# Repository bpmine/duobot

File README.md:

# duobot

## Introduction

Ce projet est un n-ième clone du célèbre "self balancing robot" que l'on peut voir un peut partout sur Internet.

Voici un lien vers le projet original: https://electricdiylab.com/diy-self-balancing-robot/

Pour ce projet, nous conservons les fondamentaux de l'original (moteur, drivers, accéléromètre, ...).

Nous utiliserons les matériaux et les outils à notre à notre disposition. Les dimensions du robot seront également les nôtres.

Et la carte sera développée dans le but d'être utilisée pour d'autres applications similaires et pour permettre la mise au point d'autres projets à base de moteurs pas-à-pas.

## Construction du robot

## Conception de la carte

### Schéma

Presque un copier-coller du modèle d'origine.

Les différences principales sont les suivantes:
- Pull up sur le Enable plutôt que des pull-down sur le Step de chaque driver;
- Branchement des M0, M1 et M2 sur l'arduino (pour permettre le réglage de la résolution);
- Possibilité de brancher soit un drv4988 (comme l'original), soit un drv8825 (broche VDD ou Fault que l'on peut connecter grâce à des résistances 0 Ohms);
- Ajout de condensateurs de découplage (comme préconisé dans la datasheet des drivers);
- Sortie des broches non utilisées sur un connecteur d'extension.

### Routage du PCB

Complètement revu pour une carte moins dense (un peu plus grande) de 100mm x 70mm.
Les connecteurs seront des borniers plutôt que des JST comme sur le modèle. Ca permet un peu plus de souplesse lors des essais...

### Vue en 3D

## Mise en service

### Réglage du courant MAX

On tourne le potentiomètre des drivers jusqu'à obtenir 1V. Cela correspond à 250mA environ. Ce réglage sera à afiner en fonction des performances et de la limite admissible par le moteur...

### Programme de test de la carte

Le programme permet de tester la carte.

- Il affiche les valeurs lues sur l'accéléromètre
- il permet d'actionner les moteurs à l'aide des commandes.

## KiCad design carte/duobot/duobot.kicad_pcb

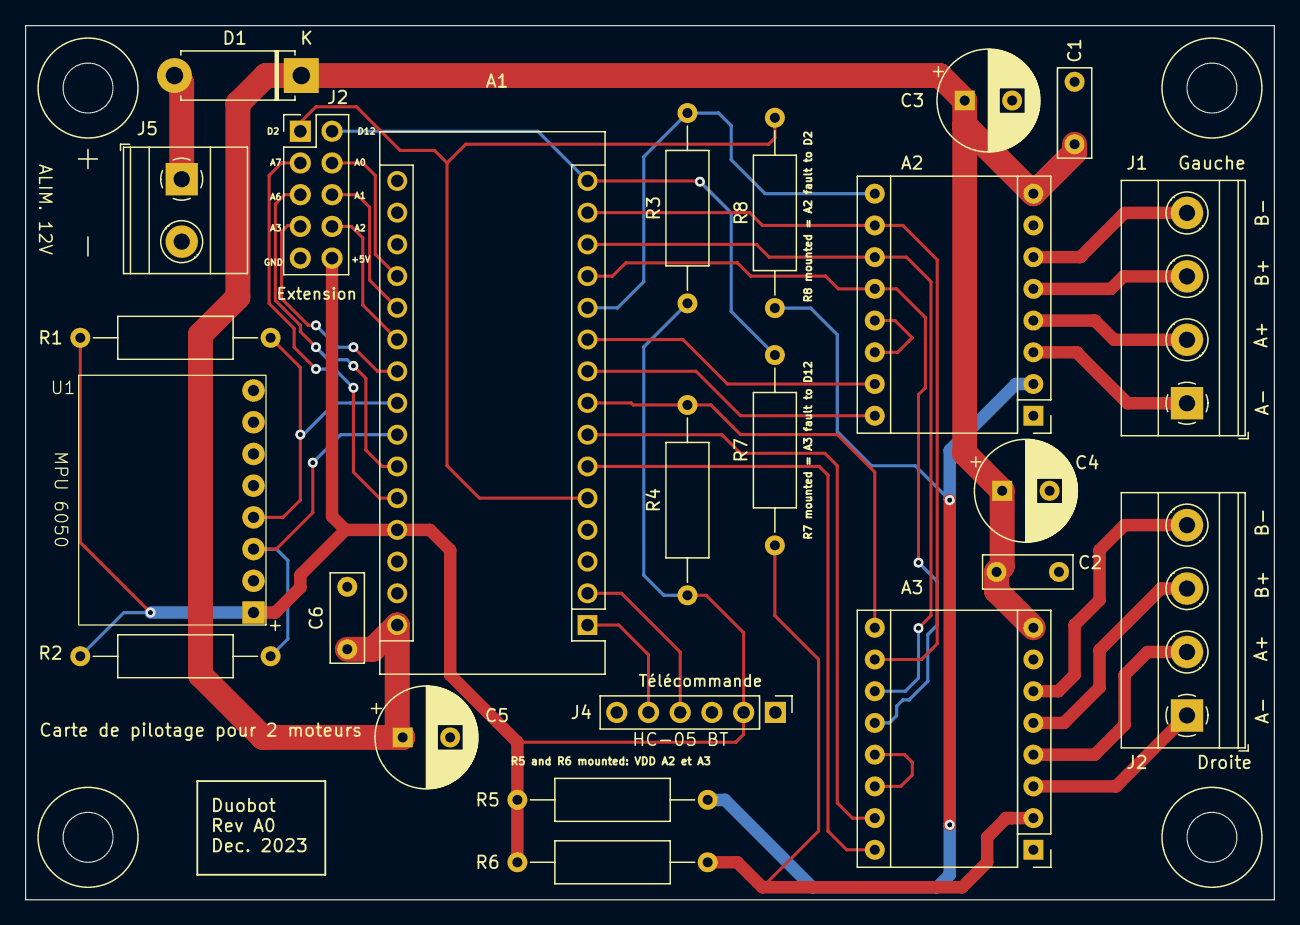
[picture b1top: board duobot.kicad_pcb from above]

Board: 2 copper layers, 100.0 x 70.0 mm, 28 parts (0 on the bottom side), 37 nets.

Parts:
A1: Arduino_Nano_v3.x; BPC_Arduino_Nano
A2, A3: BPC_Module-16_15.2x20.3mm
C1, C2: 100n; C_Disc_D7.0mm_W2.5mm_P5.00mm
C3, C4: 100uF; CP_Radial_D8.0mm_P3.80mm
C5: 20uF; CP_Radial_D8.0mm_P3.80mm
C6: 1n; C_Disc_D7.0mm_W2.5mm_P5.00mm
D1: D; D_5W_P10.16mm_Horizontal
J1: Moteur Gauche; TerminalBlock_Phoenix_MKDS-1,5-4-5.08_1x04_P5.08mm_Horizont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
J2: Moteur Droite; TerminalBlock_Phoenix_MKDS-1,5-4-5.08_1x04_P5.08mm_Horizont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
J2#2: Extension; PinHeader_2x05_P2.54mm_Vertical
J4: HC05 - BT; PinHeader_1x06_P2.54mm_Vertical
J5: Batterie; TerminalBlock_Phoenix_MKDS-1,5-2_1x02_P5.00mm_Horizontal
R1, R2: 10k; R_Axial_DIN0309_L9.0mm_D3.2mm_P15.24mm_Horizontal
R3, R4: 100k; R_Axial_DIN0309_L9.0mm_D3.2mm_P15.24mm_Horizontal
R5, R6, R7, R8: 0; R_Axial_DIN0309_L9.0mm_D3.2mm_P15.24mm_Horizontal
U1: BPC_MPU6050
X1, X2, X3, X4: Trou; BPC_Trou4mm_Fixation

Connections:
+5V: A1.27 (+5V), J2#2.10, J4.2, R1.1, R2.2, R3.1, R4.1, R5.2, R6.2, U1.1 (Vcc)
A0: A1.19 (A0), J2#2.4
A1: A1.20 (A1), J2#2.6
A2: A1.21 (A2), J2#2.8
A3: A1.22 (A3), J2#2.7
A6: A1.25 (A6), J2#2.5
A7: A1.26 (A7), J2#2.3
D2: A1.5 (D2), J2#2.1, R8.2
D12: A1.15 (D12), J2#2.2, R7.2
DIR_Droite: A1.6 (D3), A3.16 (DIR)
DIR_Gauche: A1.9 (D6), A2.16 (DIR)
EN_Droite: A1.8 (D5), A3.9 (~ENABLE), R4.2
EN_Gauche: A1.11 (D8), A2.9 (~ENABLE), R3.2
GND: A1.4 (GND), A1.29 (GND), A2.1 (GND), A2.7 (GND), A3.1 (GND), A3.7 (GND), C1.2, C2.2, C3.2, C4.2, C5.2, C6.2, J2#2.9, J4.3, J5.2, U1.2 (Gnd)
M0: A1.14 (D11), A2.10 (MS1), A3.10 (MS1)
M1: A1.13 (D10), A2.11 (MS2), A3.11 (MS2)
M2: A1.12 (D9), A2.12 (MS3), A3.12 (MS3)
unnamed: A1.2 (D0/RX), J4.4
unnamed: A1.1 (D1/TX), J4.5
unnamed: A1.30 (VIN), A2.8 (VMOT), A3.8 (VMOT), C1.1, C2.1, C3.1, C4.1, C5.1, C6.1, D1.1 (K)
unnamed: A2.4 (1A), J1.2
unnamed: A2.3 (1B), J1.1
unnamed: A2.5 (2A), J1.3
unnamed: A2.6 (2B), J1.4
unnamed: A2.2 (VDD), R5.1, R8.1
unnamed: A2.13 (~RESET), A2.14 (~SLEEP)
unnamed: A3.4 (1A), J2.2
unnamed: A3.3 (1B), J2.1
unnamed: A3.5 (2A), J2.3
unnamed: A3.6 (2B), J2.4
unnamed: A3.2 (VDD), R6.1, R7.1
unnamed: A3.13 (~RESET), A3.14 (~SLEEP)
unnamed: D1.2 (A), J5.1
SCL: A1.24 (A5), R2.1, U1.3 (SCL)
SDA: A1.23 (A4), R1.2, U1.4 (SDA)
STEP_Droite: A1.7 (D4), A3.15 (STEP)
STEP_Gauche: A1.10 (D7), A2.15 (STEP)

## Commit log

2023-12-16 Création pièce pour fixation roue
2023-12-17 Création de la carte de pilotage du robot
    Empreintes de l'accéléromètre et du module bluetooth à revoir avant envoi
2023-12-17 Finalisation routage et schéma
2023-12-17 Correction suite analyse des règles PCB
2023-12-26 Carte: Petite correction référence R5 et R8 sur le schéma Création du programme de test de la carte: OK
2023-12-29 first step to remove duplicate code
    not tested.
2023-12-29 Update duobot_test.ino
    rewriting
2023-12-29 Update duobot_test.ino
    remove repetitiion
2023-12-29 Update duobot_test.ino
    end of refactoring
2023-12-29 Update duobot_test.ino
    forget semicolon
2023-12-29 Finalisation test avec MPU +Ajout datasheet MPU + recette pour config HC 05 bluetooth
2023-12-29 Création du soft de pilotage du robot
    - Pilotage des moteurs sous IT (même vitesse des deux côtés)
    - mesure angle d'inclinaison
    Reste à faire le PiD....
2023-12-30 create inline function (syntax error, correct it at next commit)
2023-12-30 extract functions
